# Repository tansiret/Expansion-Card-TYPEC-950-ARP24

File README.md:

# Expansion-Card-TYPEC-950-ARP24
Framework Expansion Card template, with TYPEC-950-ARP24 (NextPCB's suggestion)

# License
[OG expansion card template](https://github.com/FrameworkComputer/ExpansionCards) designed by [Framework](https://frame.work). Derivative designed by: [Tan Siret Akıncı](https://github.com/tansiret).
Schematics and footprint are licensed with [CC BY 4.0](LICENSE).

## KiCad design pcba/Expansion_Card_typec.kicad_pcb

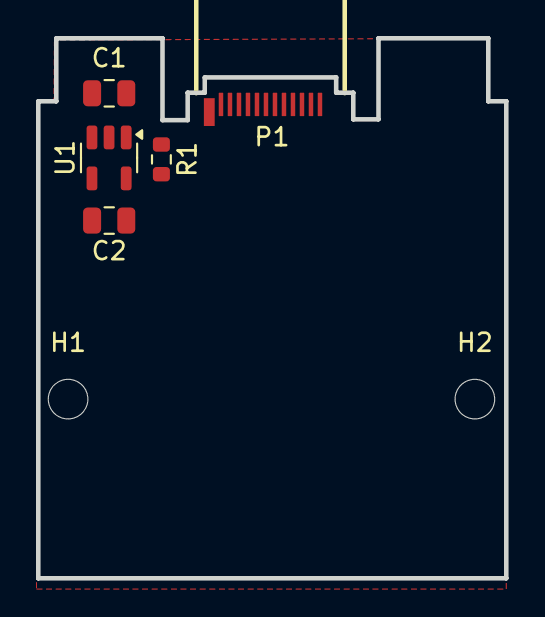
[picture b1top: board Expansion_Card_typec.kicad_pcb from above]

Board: 2 copper layers, 26.0 x 30.0 mm, 7 parts (0 on the bottom side), 4 nets, no tracks yet.

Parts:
C1, C2: 10uF; C_0805_2012Metric
H1, H2: MountingHole; MountingHole_2.2mm_M2
P1: USB_C_Plug_USB2.0; TYPEC-SMD_TYPEC-950-ARP24
R1: 5.1k; R_0603_1608Metric
U1: AP2112K-3.3; SOT-23-5

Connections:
+3.3V: C2.1, U1.5 (VOUT)
GND: C1.2, C2.2, P1.A1 (GND), P1.A12 (GND), P1.B1 (GND), P1.B12 (GND), R1.2, U1.2 (GND)
unnamed: P1.A5 (CC), R1.1
VBUS: C1.1, P1.A4 (VBUS), P1.A9 (VBUS), P1.B4 (VBUS), P1.B9 (VBUS), U1.1 (VIN), U1.3 (EN)

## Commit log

2025-09-22 initial
2025-09-22 revise edge cuts
2025-09-22 revise edge cuts more
2025-09-22 put usb more below
2025-09-23 lower type-c
2025-09-23 minor fix
2025-09-23 add image
2025-09-23 edit README
2025-09-23 fix size

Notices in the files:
pcba/Expansion_Card_typec.kicad_pcb:
This work is licensed under a Creative Commons Attribution 4.0 International License
